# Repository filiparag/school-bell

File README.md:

## Embedded School Bell System

This project is a school bell system implemented using Python on a Raspberry Pi 3 board. In addition to software control, a PCB shield was designed for easier control by school staff.

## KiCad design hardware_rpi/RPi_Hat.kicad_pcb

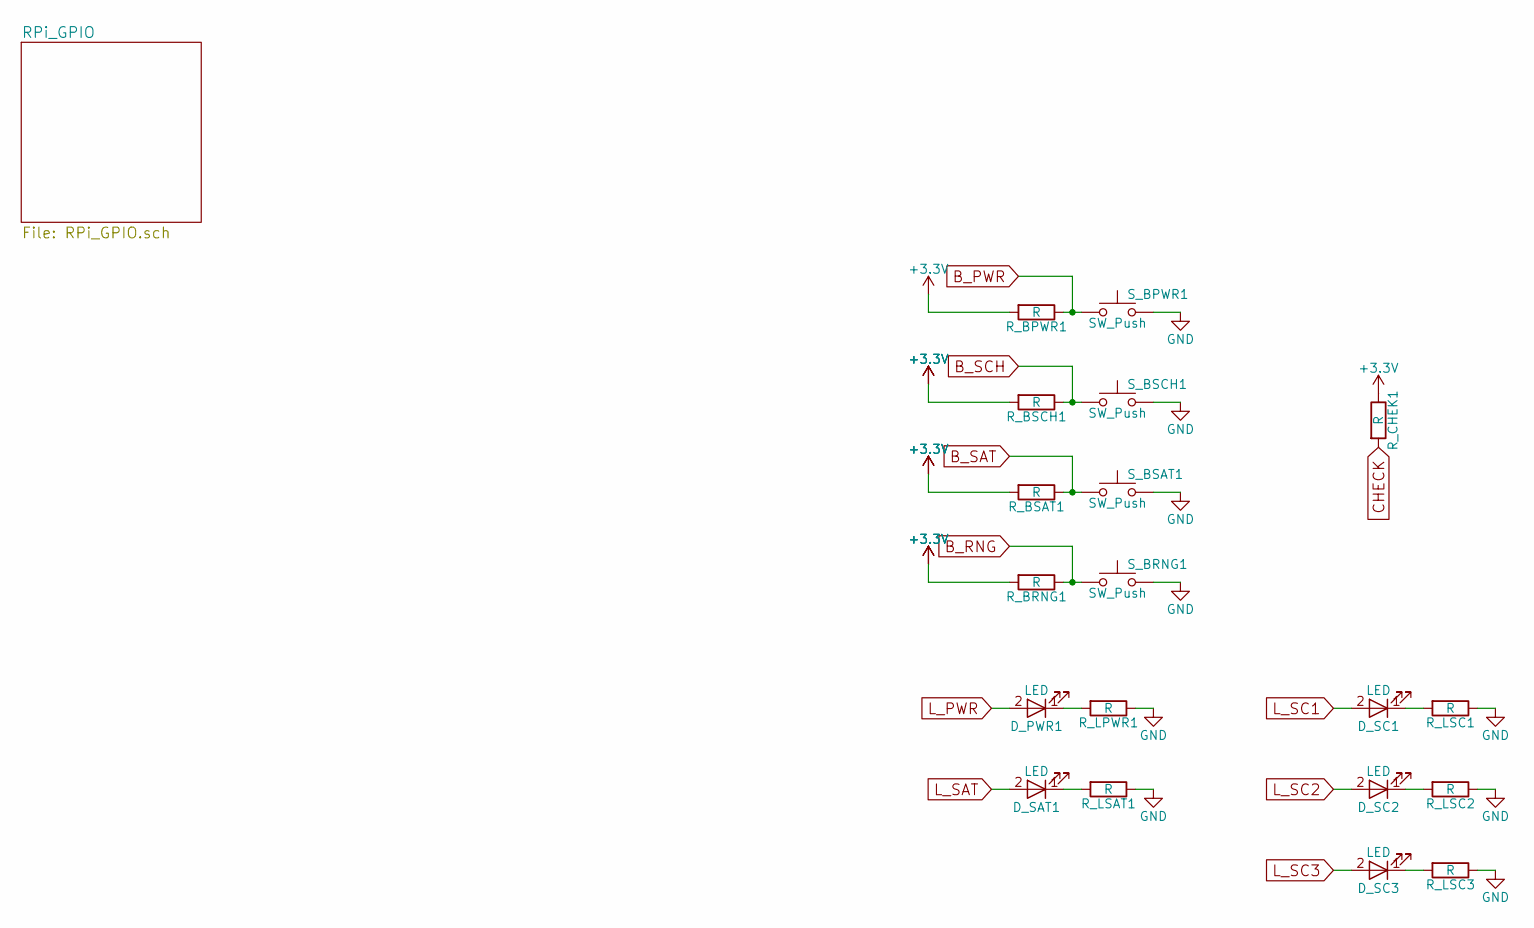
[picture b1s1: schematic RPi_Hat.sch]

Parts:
D_PWR1: LED; LED_D5.0mm
D_SAT1: LED; LED_D5.0mm
D_SC1, D_SC2, D_SC3: LED; LED_D5.0mm
R_BPWR1: R; R_2010_HandSoldering
R_BRNG1: R; R_2010_HandSoldering
R_BSAT1: R; R_2010_HandSoldering
R_BSCH1: R; R_2010_HandSoldering
R_CHEK1: R; R_2010_HandSoldering
R_LPWR1: R; R_2010_HandSoldering
R_LSAT1: R; R_2010_HandSoldering
R_LSC1, R_LSC2, R_LSC3: R; R_2010_HandSoldering
S_BPWR1: SW_Push; SW_PUSH-12mm
S_BRNG1: SW_Push; SW_PUSH-12mm
S_BSAT1: SW_Push; SW_PUSH-12mm
S_BSCH1: SW_Push; SW_PUSH-12mm

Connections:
+3V3: R_BPWR1.2, R_BRNG1.2, R_BSAT1.2, R_BSCH1.2, R_CHEK1.1; also elsewhere on the board
B_PWR: R_BPWR1.1, S_BPWR1.1; also elsewhere on the board
B_RNG: R_BRNG1.1, S_BRNG1.1; also elsewhere on the board
B_SAT: R_BSAT1.1, S_BSAT1.1; also elsewhere on the board
B_SCH: R_BSCH1.1, S_BSCH1.1; also elsewhere on the board
CHECK: R_CHEK1.2; also elsewhere on the board
GND: R_LPWR1.1, R_LSAT1.1, R_LSC1.1, R_LSC2.1, R_LSC3.1, S_BPWR1.2, S_BRNG1.2, S_BSAT1.2, S_BSCH1.2; also elsewhere on the board
L_PWR: D_PWR1.2 (A); also elsewhere on the board
L_SAT: D_SAT1.2 (A); also elsewhere on the board
L_SC1: D_SC1.2 (A); also elsewhere on the board
L_SC2: D_SC2.2 (A); also elsewhere on the board
L_SC3: D_SC3.2 (A); also elsewhere on the board
unnamed: D_PWR1.1 (K), R_LPWR1.2
unnamed: D_SAT1.1 (K), R_LSAT1.2
unnamed: D_SC1.1 (K), R_LSC1.2
unnamed: D_SC2.1 (K), R_LSC2.2
unnamed: D_SC3.1 (K), R_LSC3.2

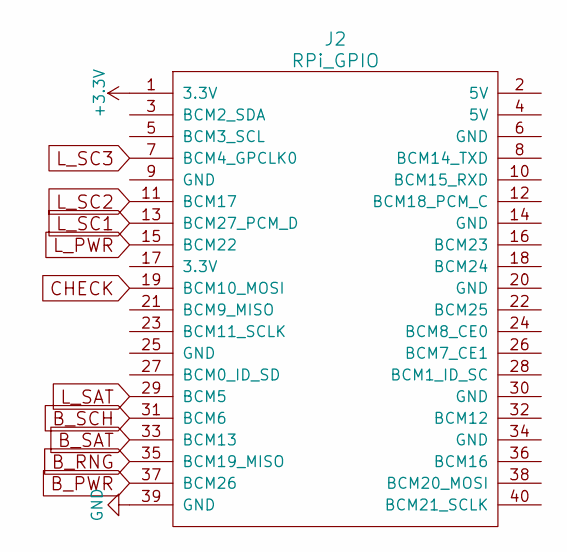
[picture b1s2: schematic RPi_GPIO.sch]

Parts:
J2: RPi_GPIO; Pin_Header_Straight_2x20

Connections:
+3V3: J2.1 (3.3V); also elsewhere on the board
B_PWR: J2.37 (BCM26); also elsewhere on the board
B_RNG: J2.35 (BCM19_MISO); also elsewhere on the board
B_SAT: J2.33 (BCM13); also elsewhere on the board
B_SCH: J2.31 (BCM6); also elsewhere on the board
CHECK: J2.19 (BCM10_MOSI); also elsewhere on the board
GND: J2.39 (GND); also elsewhere on the board
L_PWR: J2.15 (BCM22); also elsewhere on the board
L_SAT: J2.29 (BCM5); also elsewhere on the board
L_SC1: J2.13 (BCM27_PCM_D); also elsewhere on the board
L_SC2: J2.11 (BCM17); also elsewhere on the board
L_SC3: J2.7 (BCM4_GPCLK0); also elsewhere on the board

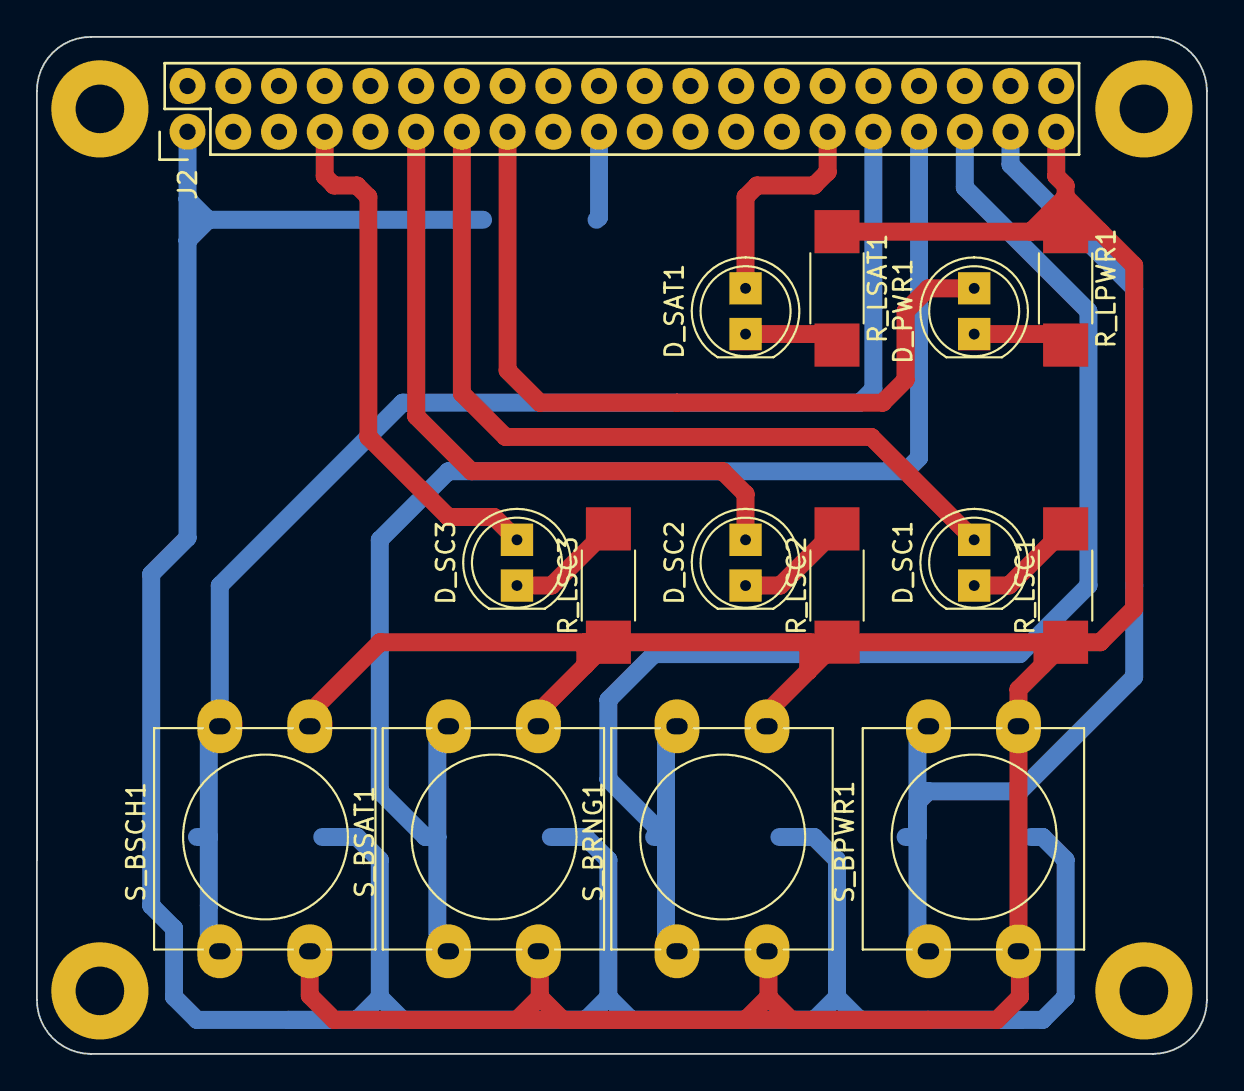
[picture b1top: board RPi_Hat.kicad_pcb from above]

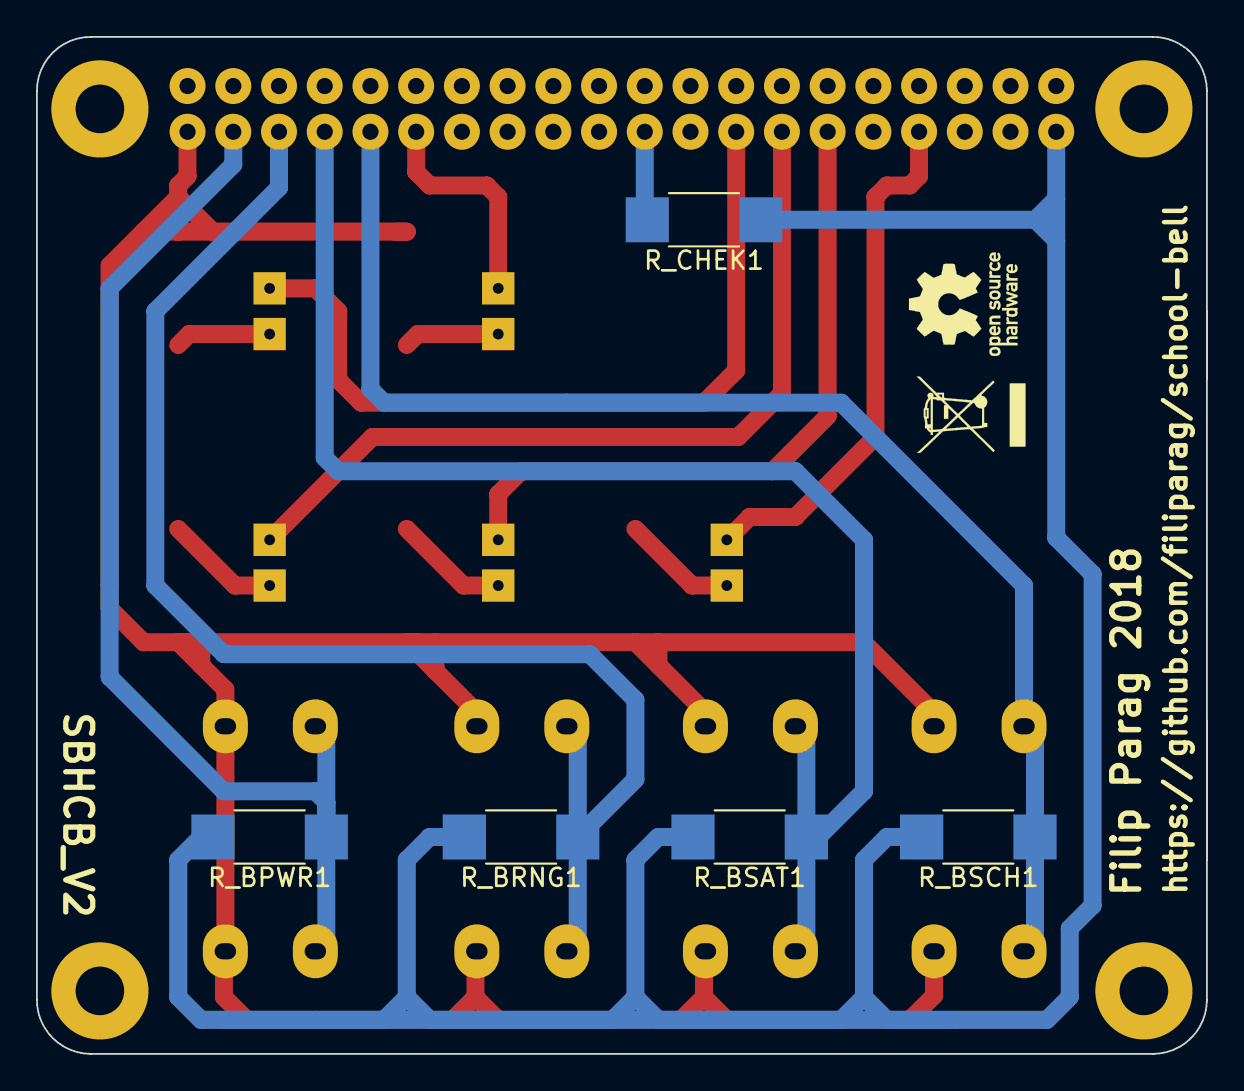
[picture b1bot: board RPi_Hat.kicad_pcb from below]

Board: 2 copper layers, 65.0 x 56.5 mm, 20 parts (5 on the bottom side), 17 nets.

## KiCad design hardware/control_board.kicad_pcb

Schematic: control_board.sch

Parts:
D_PWR1: LED; LED_D3.0mm
D_SAT1: LED; LED_D3.0mm
D_SC1, D_SC2, D_SC3: LED; LED_D3.0mm
J1: Conn_01x10_Male; Pin_Header_Angled_1x13_Pitch2.54mm
R_B_PWR1: R; R_Axial_DIN0207_L6.3mm_D2.5mm_P10.16mm_Horizontal
R_B_RNG1: R; R_Axial_DIN0207_L6.3mm_D2.5mm_P10.16mm_Horizontal
R_B_SAT1: R; R_Axial_DIN0207_L6.3mm_D2.5mm_P10.16mm_Horizontal
R_B_SCH1: R; R_Axial_DIN0207_L6.3mm_D2.5mm_P10.16mm_Horizontal
R_L_PWR1: R; R_Axial_DIN0207_L6.3mm_D2.5mm_P10.16mm_Horizontal
R_L_SAT1: R; R_Axial_DIN0207_L6.3mm_D2.5mm_P10.16mm_Horizontal
R_L_SC1, R_L_SC2, R_L_SC3: R; R_Axial_DIN0207_L6.3mm_D2.5mm_P10.16mm_Horizontal
SW_PWR1: SW_Push; SW_PUSH-12mm
SW_RNG1: SW_Push; SW_PUSH-12mm
SW_SAT1: SW_Push; SW_PUSH-12mm
SW_SCH1: SW_Push; SW_PUSH-12mm

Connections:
B_PWR: J1.16, R_B_PWR1.1, SW_PWR1.1
B_RNG: J1.19, R_B_RNG1.1, SW_RNG1.1
B_SAT: J1.18, R_B_SAT1.1, SW_SAT1.1
B_SCH: J1.17, R_B_SCH1.1, SW_SCH1.1
CHECK: J1.1, J1.9, J1.10, R_B_PWR1.2, R_B_RNG1.2, R_B_SAT1.2, R_B_SCH1.2
GND: D_PWR1.1 (K), D_SAT1.1 (K), D_SC1.1 (K), D_SC2.1 (K), D_SC3.1 (K), J1.5, J1.13, J1.20, SW_PWR1.2, SW_RNG1.2, SW_SAT1.2, SW_SCH1.2
L_PWR: J1.4, R_L_PWR1.2
L_SAT: J1.15, R_L_SAT1.2
L_SC1: J1.6, R_L_SC1.2
L_SC2: J1.7, R_L_SC2.2
L_SC3: J1.8, R_L_SC3.2
unnamed: D_PWR1.2 (A), R_L_PWR1.1
unnamed: D_SAT1.2 (A), R_L_SAT1.1
unnamed: D_SC1.2 (A), R_L_SC1.1
unnamed: D_SC2.2 (A), R_L_SC2.1
unnamed: D_SC3.2 (A), R_L_SC3.1

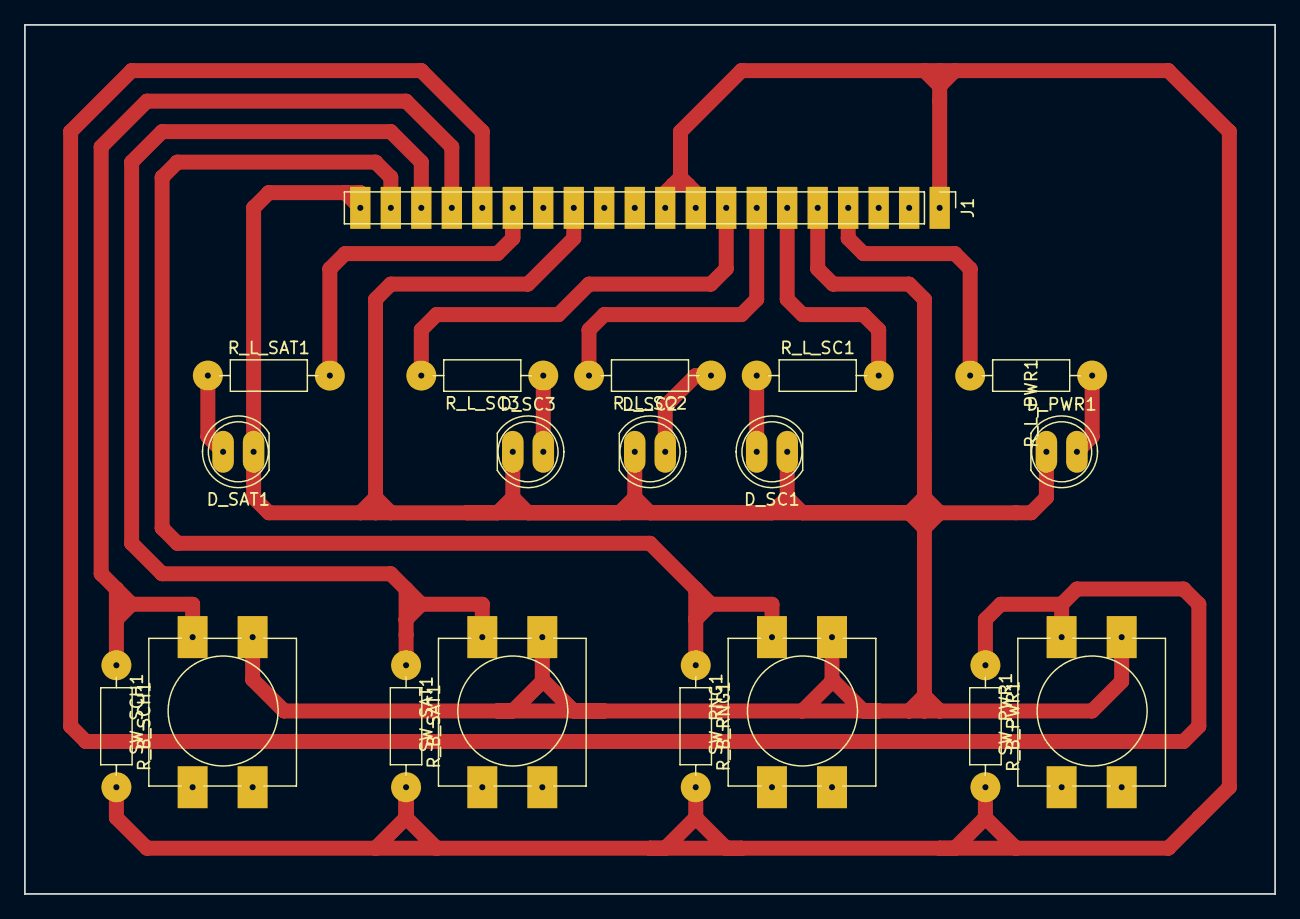
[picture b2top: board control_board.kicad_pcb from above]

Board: 2 copper layers, 104.1 x 72.4 mm, 19 parts (0 on the bottom side), 16 nets.

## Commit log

2017-09-30 Configuration
2017-09-30 School bell
2017-09-30 Config parser
2017-09-30 Schedule loader
2017-09-30 Ringer
2017-09-30 Default schedule
2017-09-30 Systemd service
2017-09-30 Bell sounds
2017-09-30 VS Code
2017-09-30 License
2017-09-30 JJZmaj schedule and sounds
2017-09-30 Indentation fix
2017-09-30 Typo
2017-09-30 Executable env change
2017-10-05 gitignore
2017-10-05 Config file
2017-10-05 Verbose and logging
2017-10-05 raspberry Pi
2017-10-05 Added RPi and logging
2017-10-05 License rename
2017-11-01 Config
2017-11-01 GPIO State
2017-11-01 Macro
2017-11-01 Schedule
2017-11-01 Empty GPIO state
2017-11-01 Test file
2017-11-01 Remove test file
2017-11-01 Updater
2017-11-01 Installer
2017-11-01 File location fix
2017-11-02 Schedules
2017-11-02 Bool fix
2017-11-02 Regular mode fix
2017-11-02 Updater log
2017-11-02 Log remove
2017-11-02 Enable GPIO
2017-11-02 Add log files to installer
2017-11-02 macro state update fix
2017-11-02 Formatting
2017-11-02 Time shift
2017-12-15 Midnight fix
2017-12-26 New control board
2017-12-26 Pinout
2017-12-26 Pickle load exception
2017-12-26 Exception
2017-12-26 Use cvlc instead of aplay
2018-01-12 Replaced triggers with polling
2018-01-12 Added sorting of schedules
2018-01-12 Experimental: PCB design for control board
2018-01-12 Removed debbuging leftovers
2018-01-12 Upgraded update.sh
2018-01-12 Macro ringer set to default instead of first
2018-01-12 Hardware
2018-01-14 Ignore .gpio_state
2018-01-14 Added new GPIO pins
2018-01-14 New Raspberry Pi mode
2018-01-14 Complete overhaul [not yet tested]
2018-01-15 Check signal connected
2018-01-21 Added RPi.GPIO code and fixed bugs
2018-01-21 Minor tweaks
2018-01-21 Saturday index fix
2018-01-21 Connection balance period
2018-01-21 Disable manual ringing when active
2018-01-21 Improved pads
2018-01-21 Added new hardware
2018-01-22 Finalized Rasberry Pi shield
2018-01-24 Prolonged default ringtone
2018-01-24 Save GPIO state
2018-01-24 Removed leftover debugging
2018-01-24 Verbose load
2018-01-24 Hotfix
2018-03-01 Remap
2018-04-14 Shift edit
2020-04-28 README
